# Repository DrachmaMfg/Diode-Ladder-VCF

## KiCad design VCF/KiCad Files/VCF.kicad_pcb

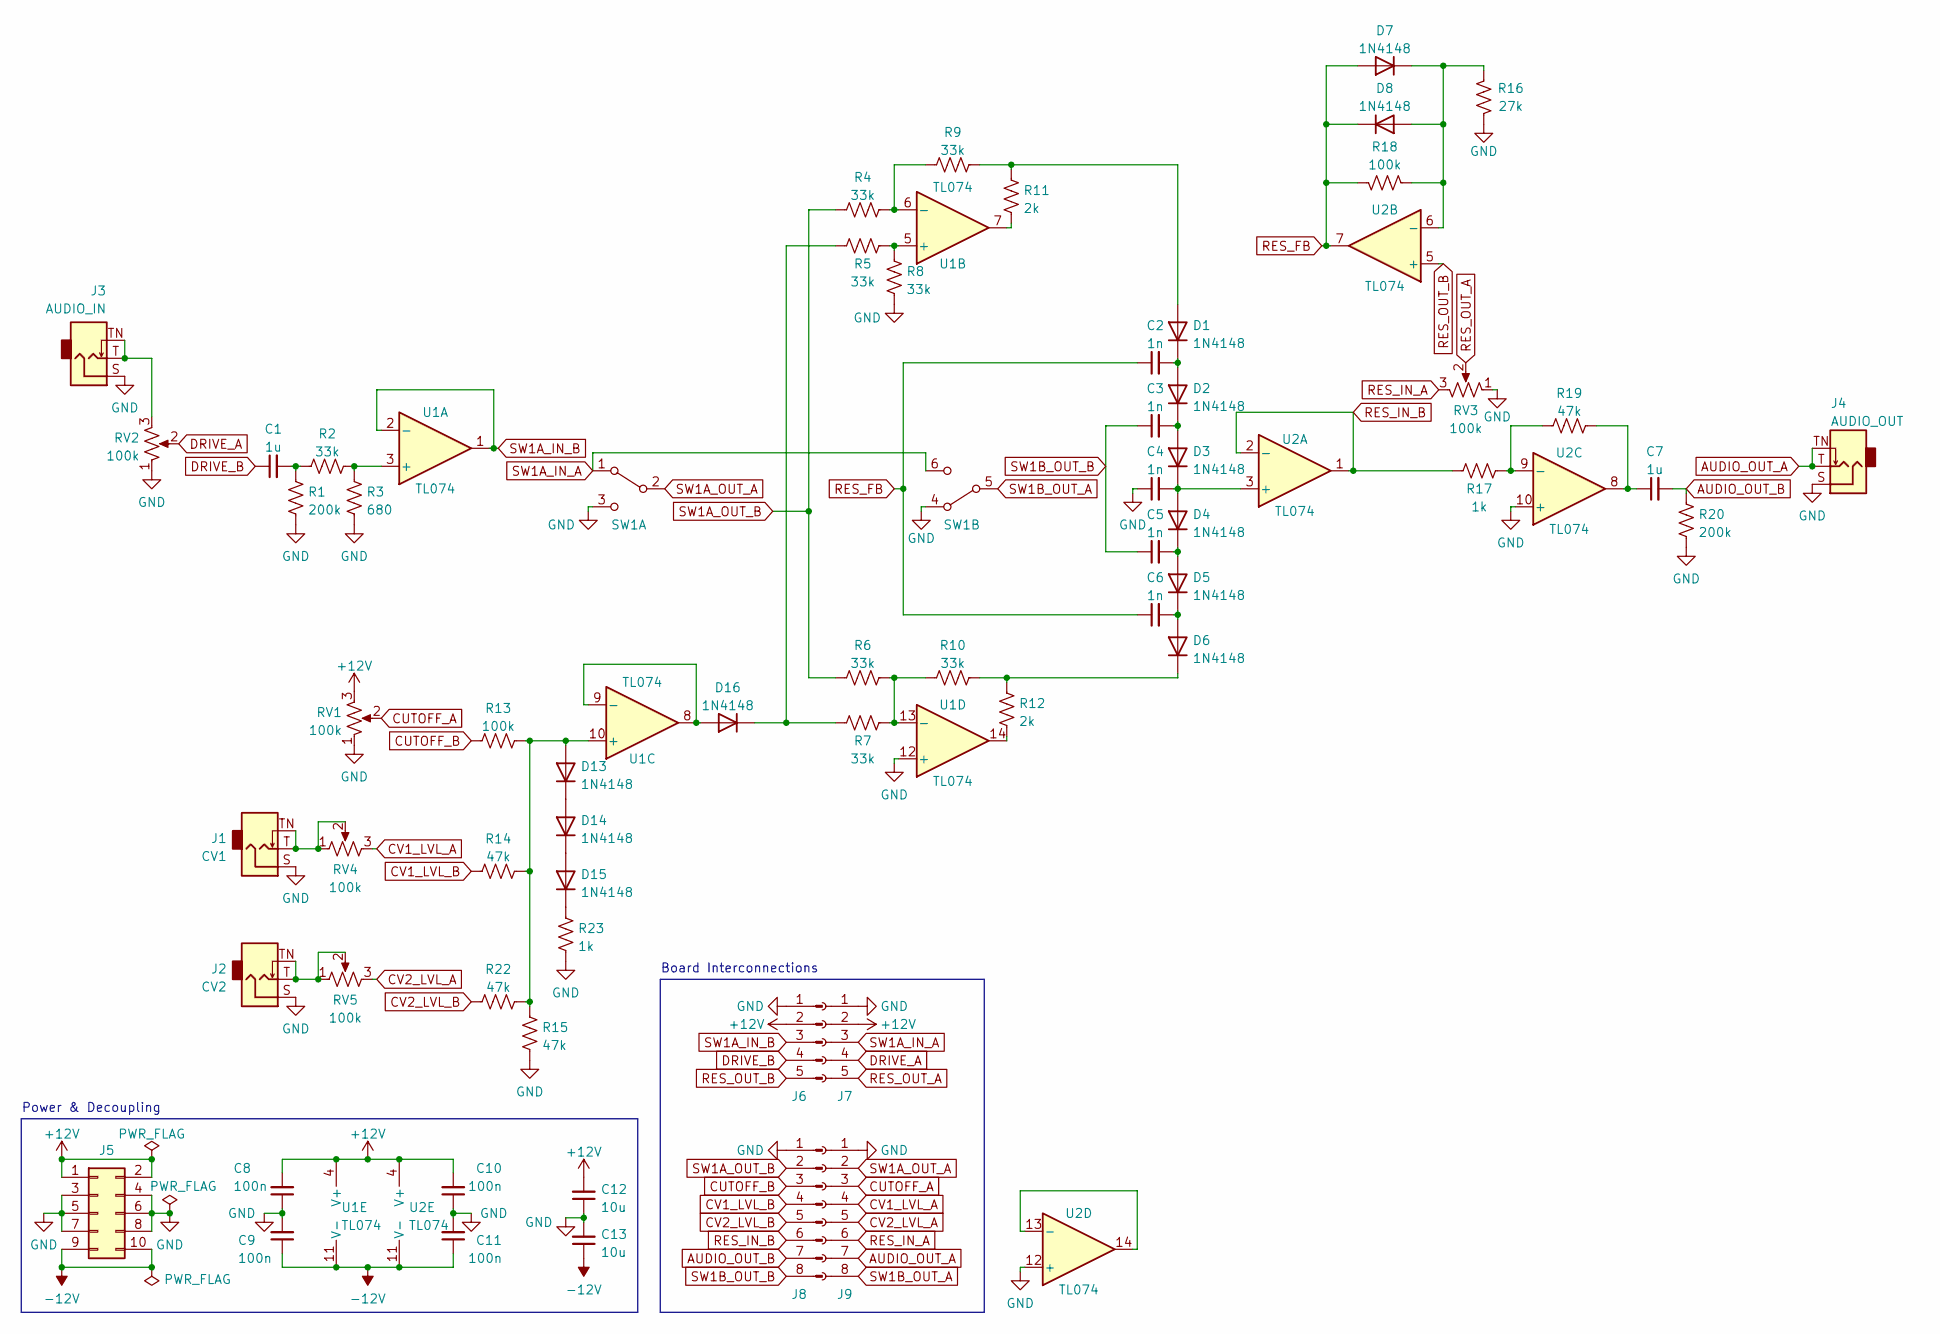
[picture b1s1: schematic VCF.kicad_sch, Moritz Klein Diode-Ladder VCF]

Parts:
C1, C7: 1u; C_Rect_L7.2mm_W3.5mm_P5.00mm_FKS2_FKP2_MKS2_MKP2
C2, C3, C4, C5, C6: 1n; C_Rect_L7.2mm_W2.5mm_P5.00mm_FKS2_FKP2_MKS2_MKP2
C8, C9, C10, C11: 100n; C_Disc_D3.8mm_W2.6mm_P2.50mm
C12, C13: 10u; CP_Radial_D5.0mm_P2.00mm
D1, D2, D3, D4, D5, D6, D7, D8, D13, D14, D15, D16: 1N4148; D_DO-35_SOD27_P7.62mm_Horizontal
J1: CV1; Jack_3.5mm_QingPu_WQP-PJ398SM_Vertical_CircularHoles_Compact
J2: CV2; Jack_3.5mm_QingPu_WQP-PJ398SM_Vertical_CircularHoles_Compact
J3: AUDIO_IN; Jack_3.5mm_QingPu_WQP-PJ398SM_Vertical_CircularHoles_Compact
J4: AUDIO_OUT; Jack_3.5mm_QingPu_WQP-PJ398SM_Vertical_CircularHoles_Compact
J5: Conn_02x05_Odd_Even; PinHeader_2x05_P2.54mm_Vertical
J6: Conn_01x05_Male; PinHeader_1x05_P2.54mm_Vertical
J7: Conn_01x05_Female; PinSocket_1x05_P2.54mm_Vertical
J8: Conn_01x08_Male; PinHeader_1x08_P2.54mm_Vertical
J9: Conn_01x08_Female; PinSocket_1x08_P2.54mm_Vertical
R1, R20: 200k; R_Axial_DIN0207_L6.3mm_D2.5mm_P7.62mm_Horizontal
R2, R4, R5, R6, R7, R8, R9, R10: 33k; R_Axial_DIN0207_L6.3mm_D2.5mm_P7.62mm_Horizontal
R3: 680; R_Axial_DIN0207_L6.3mm_D2.5mm_P7.62mm_Horizontal
R11, R12: 2k; R_Axial_DIN0207_L6.3mm_D2.5mm_P7.62mm_Horizontal
R13, R18: 100k; R_Axial_DIN0207_L6.3mm_D2.5mm_P7.62mm_Horizontal
R14, R15, R19, R22: 47k; R_Axial_DIN0207_L6.3mm_D2.5mm_P7.62mm_Horizontal
R16: 27k; R_Axial_DIN0207_L6.3mm_D2.5mm_P7.62mm_Horizontal
R17, R23: 1k; R_Axial_DIN0207_L6.3mm_D2.5mm_P7.62mm_Horizontal
RV1, RV2, RV3, RV4, RV5: 100k; Potentiometer_Alpha_Metal
SW1: SW_DPDT_x2; SW_DPDT_2MD1T2B1M1QES
U1, U2: TL074; DIP-14_W7.62mm

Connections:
+12V: C8.2, C10.2, C12.2, J5.1, J5.2, J6.2, J7.2, RV1.3, U1.4 (V+), U2.4 (V+)
-12V: C9.1, C11.1, C13.1, J5.9, J5.10, U1.11 (V-), U2.11 (V-)
AUDIO_OUT_A: J4.T, J4.TN, J9.7
AUDIO_OUT_B: C7.2, J8.7, R20.2
CUTOFF_A: J9.3, RV1.2
CUTOFF_B: J8.3, R13.1
CV1_LVL_A: J9.4, RV4.3
CV1_LVL_B: J8.4, R14.1
CV2_LVL_A: J9.5, RV5.3
CV2_LVL_B: J8.5, R22.1
DRIVE_A: J7.4, RV2.2
DRIVE_B: C1.1, J6.4
GND: C4.1, C8.1, C9.2, C10.1, C11.2, C12.1, C13.2, J1.S, J2.S, J3.S, J4.S, J5.3, J5.4, J5.5, J5.6, J5.7, J5.8, J6.1, J7.1, J8.1, J9.1, R1.1, R3.1, R8.1, R15.1, R16.1, R20.1, R23.1, RV1.1, RV2.1, RV3.1, SW1.3 (C), SW1.4 (A), U1.12 (+), U2.10 (+), U2.12 (+)
unnamed: C1.2, R1.2, R2.1
unnamed: C2.2, D1.1 (K), D2.2 (A)
unnamed: C3.2, D2.1 (K), D3.2 (A)
unnamed: C4.2, D3.1 (K), D4.2 (A), U2.3 (+)
unnamed: C5.2, D4.1 (K), D5.2 (A)
unnamed: C6.2, D5.1 (K), D6.2 (A)
unnamed: C7.1, R19.2, U2.8
unnamed: D1.2 (A), R9.2, R11.2
unnamed: D6.1 (K), R10.2, R12.2
unnamed: D7.1 (K), D8.2 (A), R16.2, R18.1, U2.6 (-)
unnamed: D13.1 (K), D14.2 (A)
unnamed: D13.2 (A), R13.2, R14.2, R15.2, R22.2, U1.10 (+)
unnamed: D14.1 (K), D15.2 (A)
unnamed: D15.1 (K), R23.2
unnamed: D16.1 (K), R5.1, R7.1
unnamed: D16.2 (A), U1.8, U1.9 (-)
unnamed: J1.T, J1.TN, RV4.1, RV4.2
unnamed: J2.T, J2.TN, RV5.1, RV5.2
unnamed: J3.T, J3.TN, RV2.3
unnamed: R2.2, R3.2, U1.3 (+)
unnamed: R4.2, R9.1, U1.6 (-)
unnamed: R5.2, R8.2, U1.5 (+)
unnamed: R6.2, R7.2, R10.1, U1.13 (-)
unnamed: R11.1, U1.7
unnamed: R12.1, U1.14
unnamed: R17.2, R19.1, U2.9 (-)
unnamed: U2.13 (-), U2.14
RES_FB: C2.1, C6.1, D7.2 (A), D8.1 (K), R18.2, U2.7
RES_IN_A: J9.6, RV3.3
RES_IN_B: J8.6, R17.1, U2.1, U2.2 (-)
RES_OUT_A: J7.5, RV3.2
RES_OUT_B: J6.5, U2.5 (+)
SW1A_IN_A: J7.3, SW1.1 (A), SW1.6 (C)
SW1A_IN_B: J6.3, U1.1, U1.2 (-)
SW1A_OUT_A: J9.2, SW1.2 (B)
SW1A_OUT_B: J8.2, R4.1, R6.1
SW1B_OUT_A: J9.8, SW1.5 (B)
SW1B_OUT_B: C3.1, C5.1, J8.8

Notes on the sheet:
Board Interconnections
Power & Decoupling

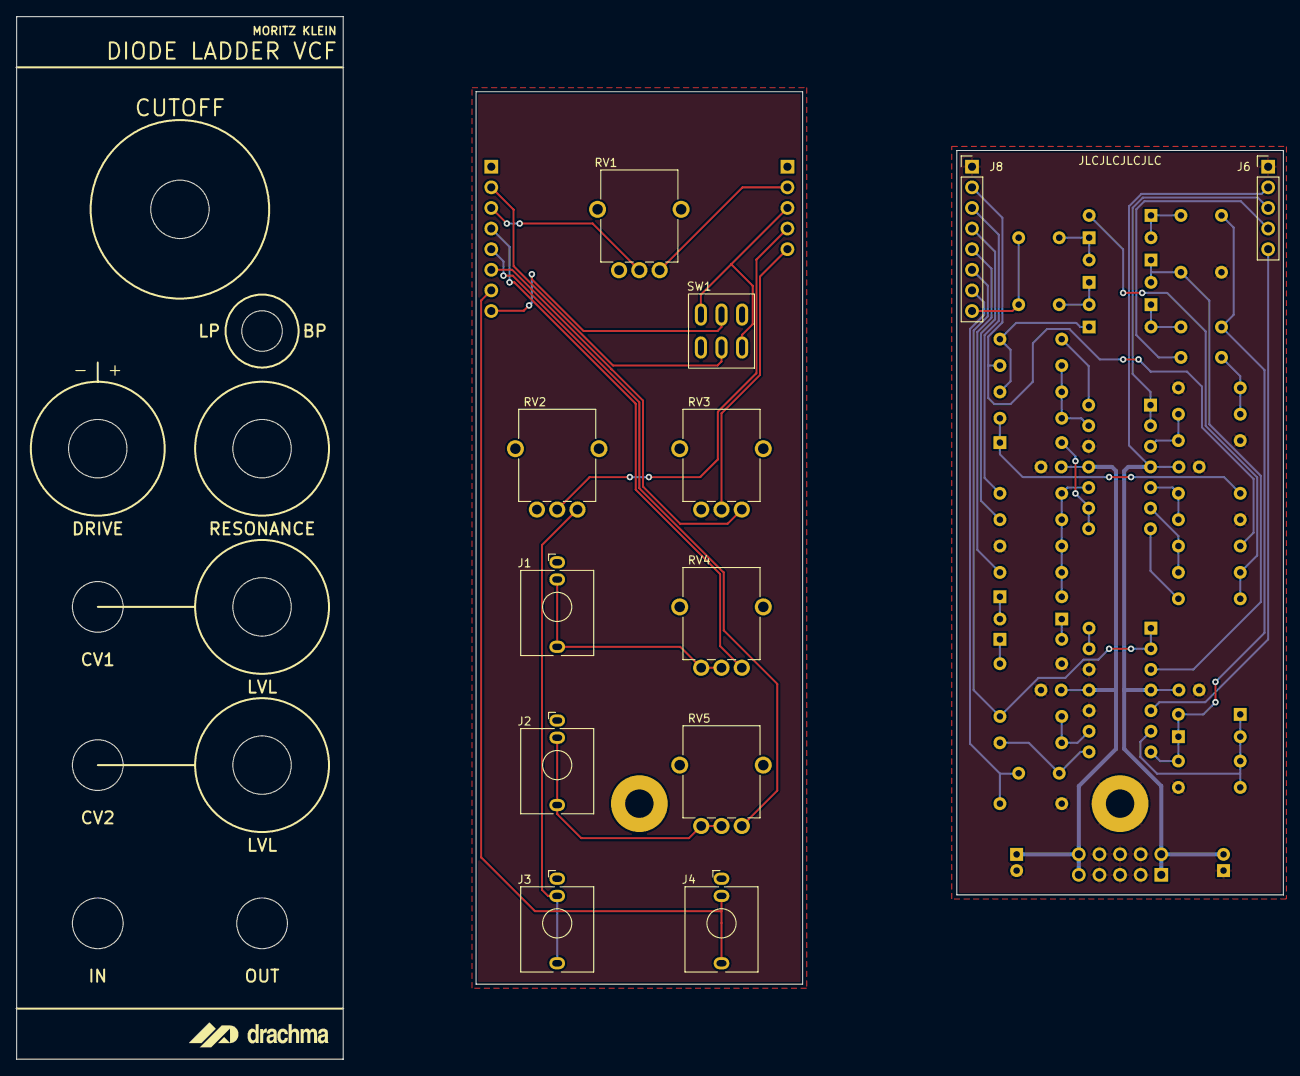
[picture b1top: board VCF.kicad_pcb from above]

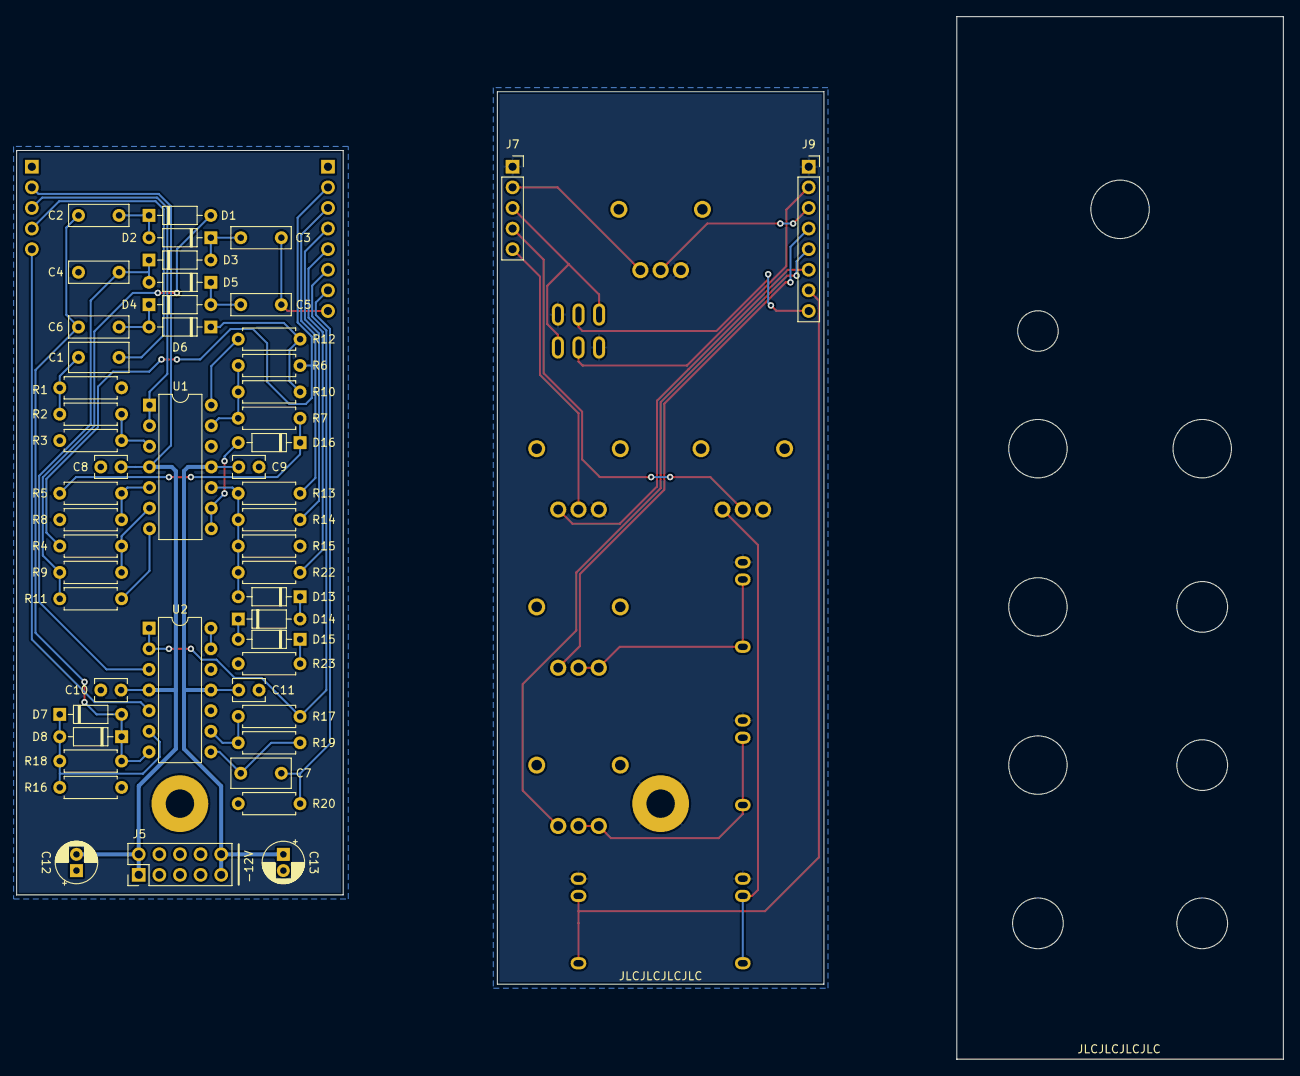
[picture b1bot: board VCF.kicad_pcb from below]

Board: 2 copper layers, 156.1 x 128.5 mm, 65 parts (52 on the bottom side), 51 nets.

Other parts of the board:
Ref**: Val**; logo_drachma_full_final_for_PCB

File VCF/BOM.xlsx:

| Value | Qty | Name on Board | Description | Footprint
 | 680R | 1 | R3 | 680R 1% 0.125W Resistor | 0805
 | 1k | 2 | R17, R23 | 1k 1% 0.125W Resistor | 0805
 | 2k | 2 | R11, R12 | 2k 1% 0.125W Resistor | 0805
 | 27k | 1 | R16 | 27k 1% 0.125W Resistor | 0805
 | 33k | 8 | R2, R4, R5, R6, R7, R8, R9, R10 | 33k 1% 0.125W Resistor | 0805
 | 47k | 4 | R14, R15, R19, R22 | 47k 1% 0.125W Resistor | 0805
 | 100k | 2 | R13, R18 | 100k 1% 0.125W Resistor | 0805
 | 200k | 2 | R1, R20 | 200k 1% 0.125W Resistor | 0805
 | 1n | 5 | C2, C3, C4, C5, C6 | 1n 50V MLCC | 0805
 | 100n | 4 | C8, C9, C10, C11 | 100n 50V MLCC | 0805
 | 1u | 2 | C1, C7 | 1u 50V MLCC | 1206
 | 10u | 2 | C12, C13 | 10u 50V Electrolytic | 5x5.4mm SMD
 | 1N4148 | 12 | D1, D2, D3, D4, D5, D6, D7, D8, D13, D14, D15, D16 | 1n4148 Gen. Purpose Diode | SOD-323
 | TL074 | 2 | U1, U2 | TL074 Quad Op-Amp | SOIC-14 3.9x8.7mm P1.27mm
 | 3.5mm Jack | 4 | J1, J2, J3, J4 | 3.5mm Mono Jack | PJ-3001F
 | B100k Pot. | 5 | RV1, RV2, RV3, RV4, RV5 | 100k Linear Potentiometer | Alpha 9mm
 | DPDT Switch | 1 | SW1 | DPDT Sub Mini Toggle Switch On-On | 2M DPDT Switch
 | 4-Pin Header, Male | 1 | J6 | 4-Pin Header Male P2.54mm | 2.54mm 4-Pin Vertical
 | 4-Pin Header, Female | 1 | J7 | 4-Pin Header Female P2.54mm | 2.54mm 4-Pin Vertical
 | 8-Pin Header, Male | 1 | J8 | 8-Pin Header Male P2.54mm | 2.54mm 8-Pin Vertical
 | 8-Pin Header, Female | 1 | J9 | 8-Pin Header Female P2.54mm | 2.54mm 8-Pin Vertical

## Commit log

2023-01-21 Added KiCad files
2023-01-21 Create LICENSE
2023-01-22 Rename VCF/.gitignore to .gitignore
2023-01-22 Updated PCBs
2023-01-22 Updated directory organization
2023-01-22 Added board Gerber files
2023-01-22 Corrected PCB
2023-01-22 Added gerber files
2023-01-22 Cleaned up schematic
2023-01-22 Added PDF schematic
2023-01-23 Added BOM
2023-01-23 Updated panel
2023-01-24 Corrected footprints
2023-01-24 Added PDF BOM
2023-01-24 Updated silkscreens
